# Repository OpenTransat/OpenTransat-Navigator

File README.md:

# OpenTransat-Navigator
The brain of the boat responsible for navigation.

## Features

* Based on Atmega2560 @ 16 MHz

* Over-the-air programming using ESP8266 flashed with Wifi-serial bridge [esp-link](https://github.com/jeelabs/esp-link)

* 9-axis accelerometer / gyro / compass

* Voltage / current sensor

* 16 Mbit flash

* 2 Mbit FRAM

* Temperature / pressure / humidity sensor

* Serial multiplexer

## Boat Hardware Scheme

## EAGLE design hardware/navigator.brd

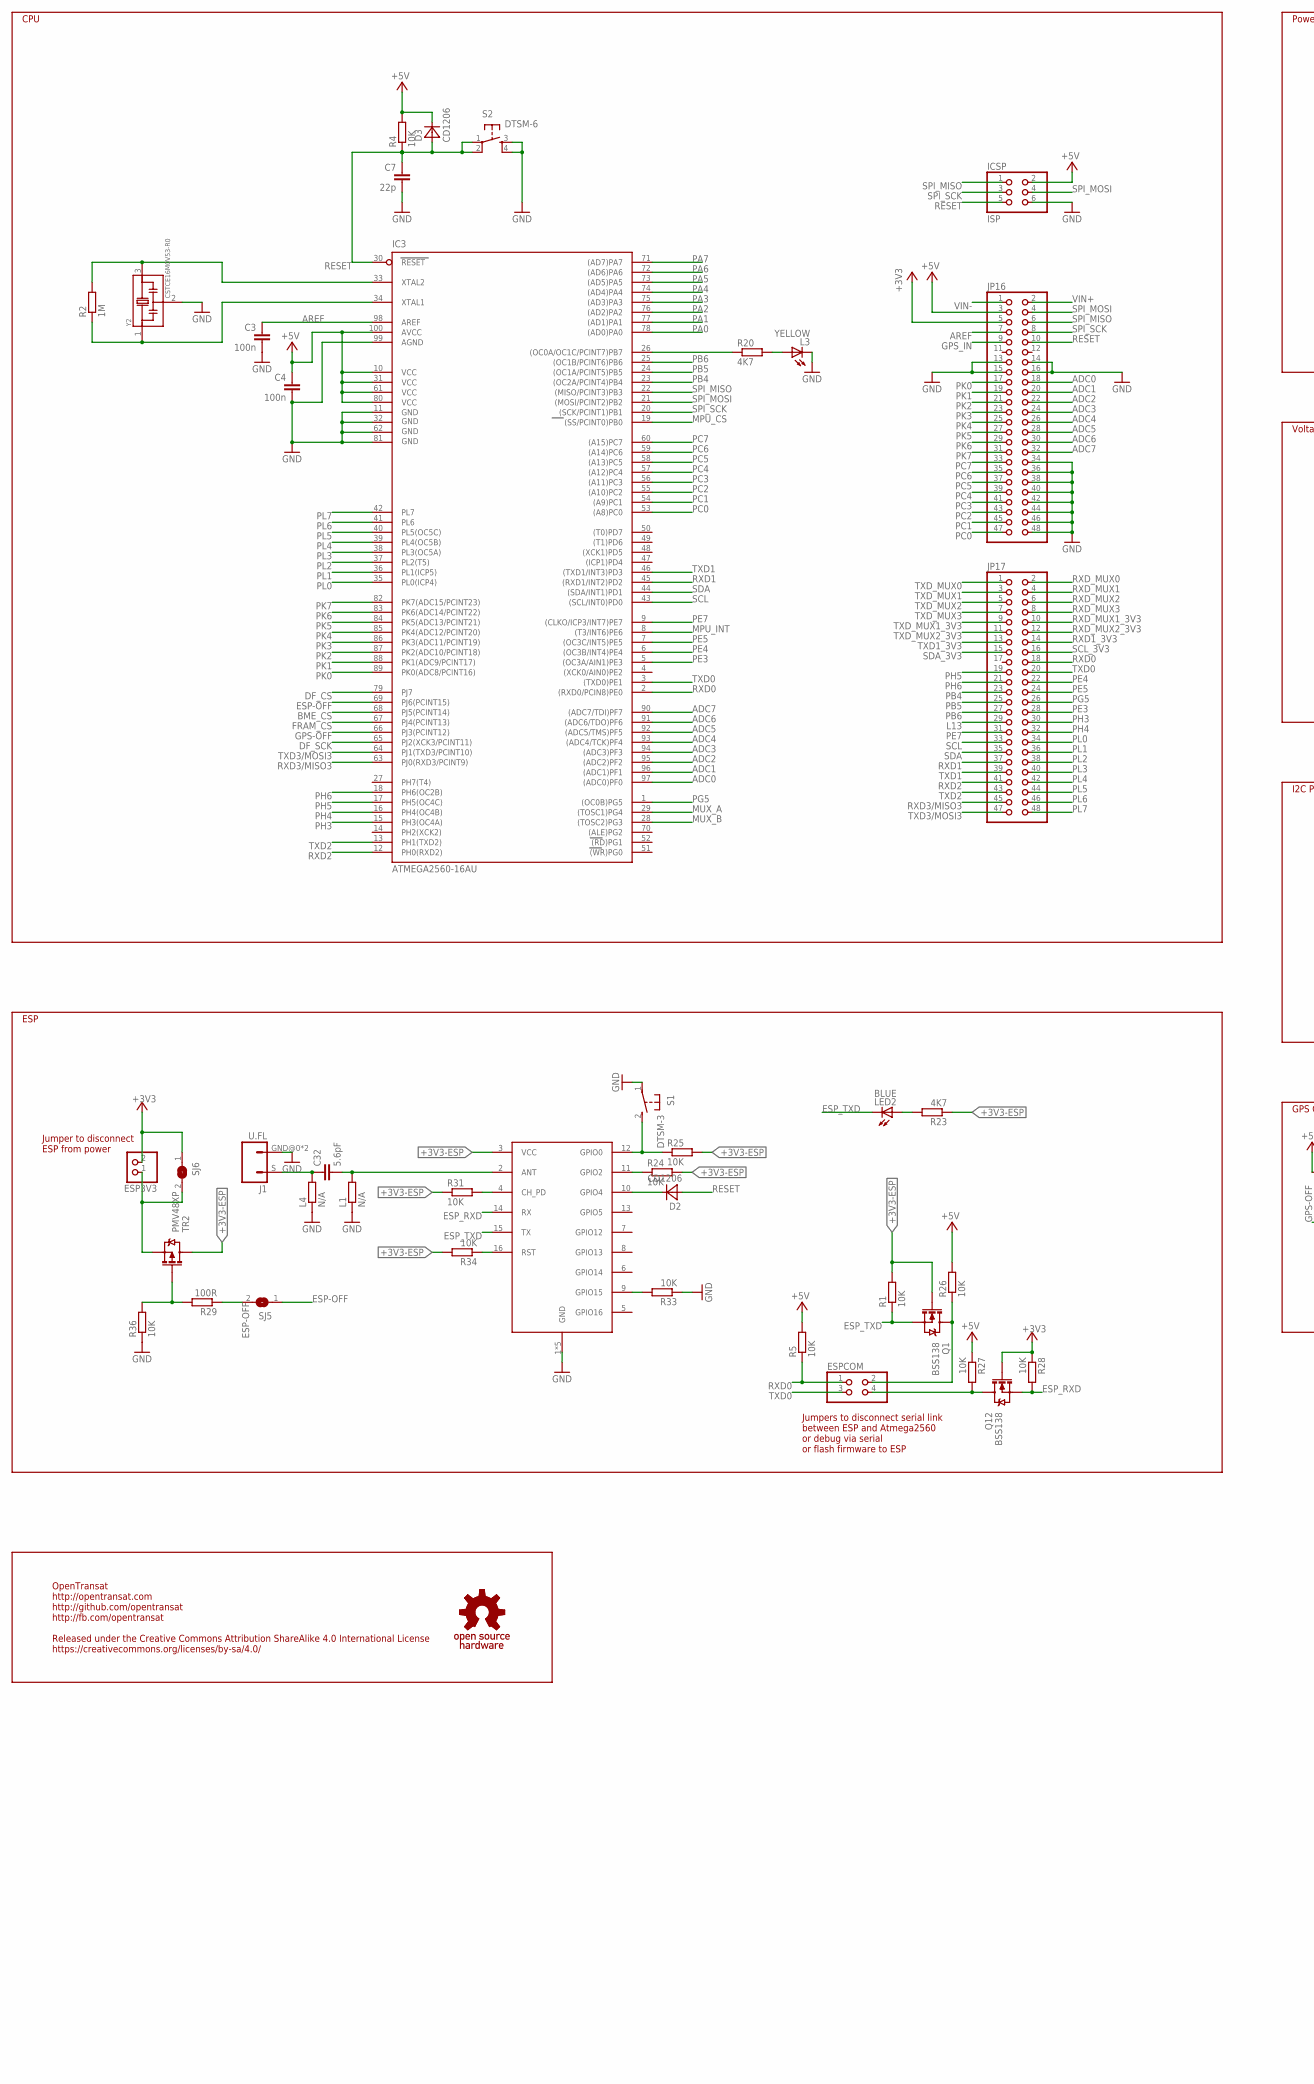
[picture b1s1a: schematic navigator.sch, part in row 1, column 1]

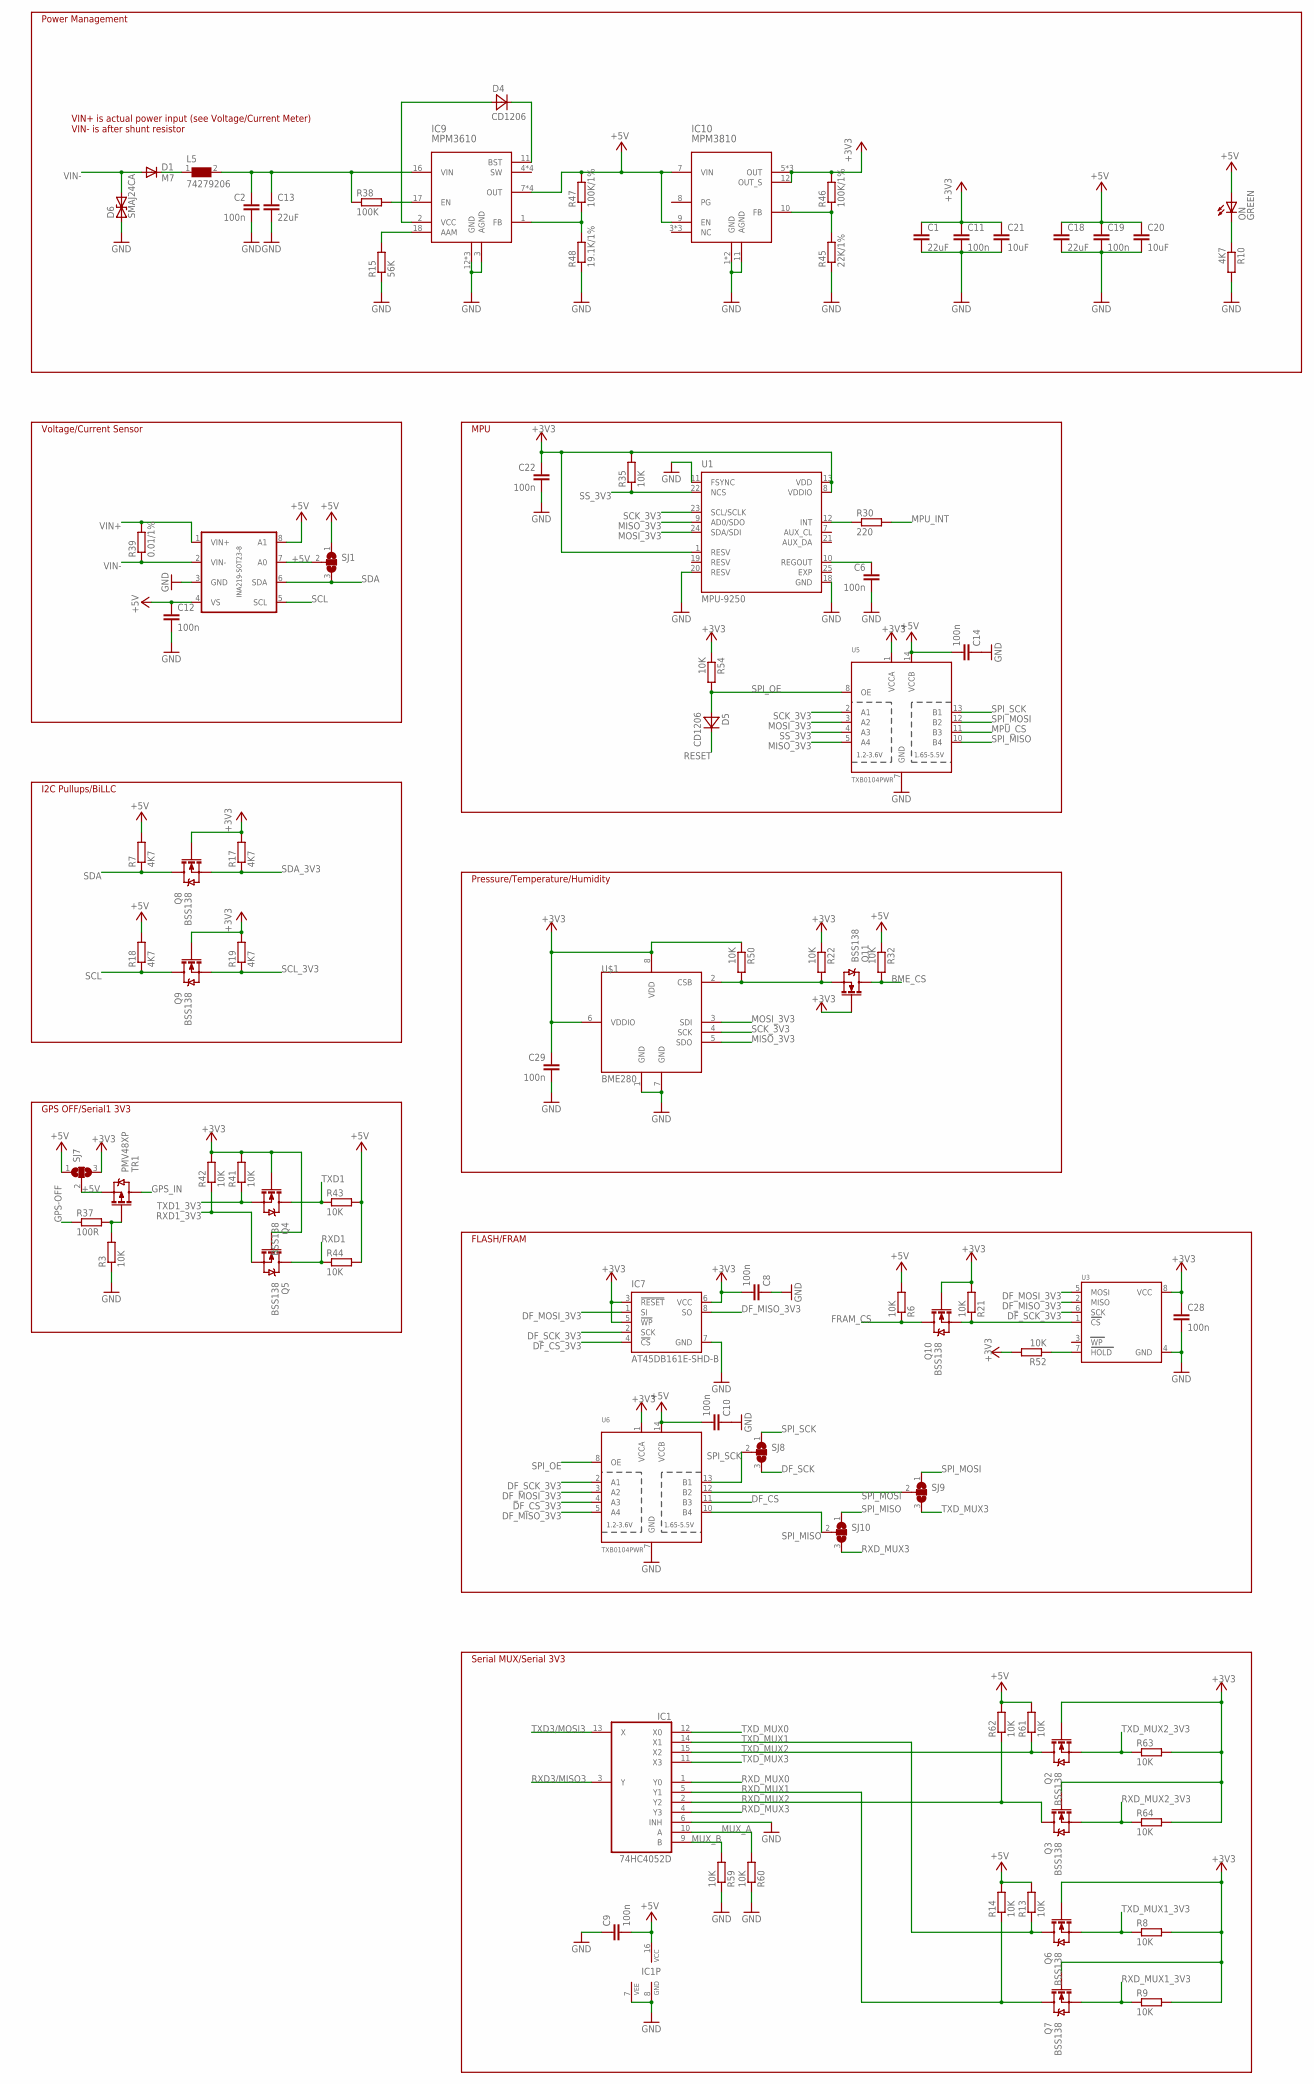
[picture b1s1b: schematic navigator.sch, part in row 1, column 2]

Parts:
C1, C13, C18: 22uF; C1210
C2, C3, C4, C6, C8, C9, C10, C11, C12, C14, C19, C22, C28, C29: 100n; C0603
C7: 22p; C0603
C20, C21: 10uF; C1206
C32: 5.6pF; C0603
D1: M7; DO-214AC
D2, D3, D4, D5: CD1206; R1206
D6: SMAJ24CA; DO214AC
ESP3V3: PINHD-1X2; 1X02
ESPCOM: PINHD-2X2; 2X02
IC1: 74HC4052D; SO16
IC3: ATMEGA2560-16AU; TQFP100
IC7: AT45DB161E-SHD-B; 8S2
IC9: MPM3610; MPM_QFN20
IC10: MPM3810; MPM_QFN12
ICSP: ISP; 2X03
J1: U.FL; CON-U.FL
JP16, JP17: PINHD-2X24; 2X24
L1, L4: N/A; R0402
L3: YELLOW; CHIPLED_0805
L5: 74279206; 0805
LED2: BLUE; CHIPLED_0805
ON: GREEN; CHIPLED_0805
Q1, Q2, Q3, Q4, Q5, Q6, Q7, Q8, Q9, Q10, Q11, Q12: BSS138; SOT23-3
R1, R3, R4, R5, R6, R8, R9, R13, R14, R21, R22, R24, R25, R26, R27, R28, R31, R32, R33, R34, R35, R36, R41, R42, R43, R44, R50, R52, R54, R59, R60, R61, R62, R63, R64: 10K; R0603
R2: 1M; R0603
R7, R10, R17, R18, R19, R20, R23: 4K7; R0603
R15: 56K; R0603
R29, R37: 100R; R0603
R30: 220; R0603
R38: 100K; R0603
R39: 0.01/1%; R2512
R45: 22K/1%; R0603
R46, R47: 100K/1%; R0603
R48: 19.1K/1%; R0603
S1: DTSM-3
S2: DTSM-6
SJ1, SJ7, SJ8, SJ9, SJ10: SJ2W; SJ_2
SJ5, SJ6: SJ
TR1, TR2: PMV48XP; SOT23-3
U1: MPU-9250; QFN40P300X300X105-25N
U3: FRAM_SOIC8_200MIL_SPI; SOIC8_200MIL
U5, U6: TXB0104PWR; TSSOP14
U$1: BME280
U$2: ESP-06
U$3: INA219-SOT23-8; SOT23-8
U$4: OSHW; OSHWM
Y2: CSTCE16M0V53-R0; OSC_CSTCE16M0V53-R0

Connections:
+3V3: C1.1, C8.2, C11.1, C21.1, C22.1, C28.1, C29.1, ESP3V3.2, IC7.3 (!RESET), IC7.5 (!WP), IC7.6 (VCC), IC10.5 (OUT), IC10.6 (OUT), IC10.12 (OUT_S), IC10.14 (OUT), JP16.5, Q2.1 (G), Q3.1 (G), Q4.1 (G), Q5.1 (G), Q6.1 (G), Q7.1 (G), Q8.1 (G), Q9.1 (G), Q10.1 (G), Q11.1 (G), Q12.1 (G), R8.2, R9.2, R17.2, R19.2, R21.2, R22.1, R28.1, R35.2, R41.2, R42.2, R46.2, R50.1, R52.2, R54.1, R63.2, R64.2, SJ6.1, SJ7.3, U1.1 (RESV), U1.8 (VDDIO), U1.13 (VDD), U3.8 (VCC), U5.1 (VCCA), U6.1 (VCCA), U$1.6 (VDDIO), U$1.8 (VDD)
+3V3-ESP: Q1.1 (G), R1.2, R23.1, R24.2, R25.2, R31.1, R34.2, TR2.3 (D), U$2.3 (VCC)
+5V: C4.1, C9.2, C10.2, C12.1, C14.2, C18.1, C19.1, C20.1, D3.2 (C), IC1.16 (VCC), IC3.10 (VCC), IC3.31 (VCC1), IC3.61 (VCC2), IC3.80 (VCC3), IC3.100 (AVCC), IC9.7 (OUT), IC9.8 (OUT), IC9.9 (OUT), IC9.20 (OUT), IC10.7 (VIN), IC10.9 (EN), ICSP.2, JP16.3, ON.A, R4.2, R5.2, R6.2, R7.2, R13.2, R14.2, R18.2, R26.2, R27.1, R32.1, R43.2, R44.2, R47.2, R61.2, R62.2, SJ1.1, SJ1.2, SJ7.1, SJ7.2, TR1.2 (S), U5.14 (VCCB), U6.14 (VCCB), U$3.4 (VS), U$3.7 (A0), U$3.8 (A1)
ADC0: IC3.97 ((ADC0)PF0), JP16.18
ADC1: IC3.96 ((ADC1)PF1), JP16.20
ADC2: IC3.95 ((ADC2)PF2), JP16.22
ADC3: IC3.94 ((ADC3)PF3), JP16.24
ADC4: IC3.93 ((ADC4/TCK)PF4), JP16.26
ADC5: IC3.92 ((ADC5/TMS)PF5), JP16.28
ADC6: IC3.91 ((ADC6/TDO)PF6), JP16.30
ADC7: IC3.90 ((ADC7/TDI)PF7), JP16.32
AREF: C3.1, IC3.98 (AREF), JP16.7
BME_CS: IC3.68 (PJ5(PCINT14)), Q11.3 (D), R32.2
DF_CS: IC3.79 (PJ7), U6.11 (B3)
DF_CS_3V3: IC7.4 (!CS), U6.4 (A3)
DF_MISO_3V3: IC7.8 (SO), U3.2 (MISO), U6.5 (A4)
DF_MOSI_3V3: IC7.1 (SI), U3.5 (MOSI), U6.3 (A2)
DF_SCK: IC3.65 (PJ2(XCK3/PCINT11)), SJ8.3
DF_SCK_3V3: IC7.2 (SCK), U3.6 (SCK), U6.2 (A1)
ESP-OFF: IC3.69 (PJ6(PCINT15)), R29.1, SJ5.1, SJ5.2
ESP_RXD: Q12.2 (S), R28.2, U$2.14 (RX)
ESP_TXD: LED2.C, Q1.2 (S), R1.1, U$2.15 (TX)
EXP: U1.25 (EXP)
FRAM_CS: IC3.67 (PJ4(PCINT13)), Q10.3 (D), R6.1
GND: C1.2, C2.2, C3.2, C4.2, C6.2, C7.2, C8.1, C9.1, C10.1, C11.2, C12.2, C13.2, C14.1, C18.2, C19.2, C20.2, C21.2, C22.2, C28.2, C29.2, D6.A (1), IC1.6 (INH), IC1.7 (VEE), IC1.8 (GND), IC3.11 (GND), IC3.32 (GND1), IC3.62 (GND2), IC3.81 (GND3), IC3.99 (AGND), IC7.7 (GND), IC9.3 (AGND), IC9.12 (GND), IC9.13 (GND), IC9.14 (GND), IC10.1 (GND), IC10.2 (GND), IC10.11 (AGND), ICSP.6, J1.GND@0 (2), J1.GND@1 (2), JP16.13, JP16.14, JP16.15, JP16.16, JP16.34, JP16.36, JP16.38, JP16.40, JP16.42, JP16.44, JP16.46, JP16.48, L1.1, L3.C, L4.1, R3.1, R10.2, R15.1, R33.1, R36.1, R45.1, R48.1, R59.1, R60.1, S1.1, S2.3, S2.4, U1.11 (FSYNC), U1.18 (GND), U1.20 (RESV), U3.4 (GND), U5.7 (GND), U6.7 (GND), U$1.1 (GND), U$1.7 (GND), U$2.1 (GND), U$2.17 (GND), U$2.18 (GND), U$2.19 (GND), U$2.20 (GND), U$3.3 (GND), Y2.2
GPS-OFF: IC3.66 (PJ3(PCINT12)), R37.1
GPS_IN: JP16.9, TR1.3 (D)
L13: IC3.26 ((OC0A/OC1C/PCINT7)PB7), JP17.29, R20.1
MISO_3V3: U1.9 (AD0/SDO), U5.5 (A4), U$1.5 (SDO)
MOSI_3V3: U1.24 (SDA/SDI), U5.3 (A2), U$1.3 (SDI)
MPU_CS: IC3.19 ((SS/PCINT0)PB0), U5.11 (B3)
MPU_INT: IC3.8 ((T3/INT6)PE6), R30.2
MUX_A: IC1.10 (A), IC3.29 ((TOSC1)PG4), R60.2
MUX_B: IC1.9 (B), IC3.28 ((TOSC2)PG3), R59.2
unnamed: ESP3V3.1, SJ6.2, TR2.2 (S)
unnamed: R52.1, U3.7 (HOLD)
unnamed: ON.C, R10.1
unnamed: L3.A, R20.2
unnamed: D4.1 (A), IC9.2 (VCC)
unnamed: D4.2 (C), IC9.11 (BST)
unnamed: LED2.A, R23.2
unnamed: R31.2, U$2.4 (CH_PD)
unnamed: R24.1, U$2.11 (GPIO2)
unnamed: D2.2 (C), U$2.10 (GPIO4)
unnamed: R33.2, U$2.9 (GPIO15)
unnamed: C32.1, J1.S (1), L4.2
unnamed: R25.1, S1.2, U$2.12 (GPIO0)
unnamed: R34.1, U$2.16 (RST)
unnamed: C32.2, L1.2, U$2.2 (ANT)
unnamed: Q10.2 (S), R21.1, U3.1 (CS)
unnamed: IC10.10 (FB), R45.2, R46.1
unnamed: ESPCOM.2, Q1.3 (D), R26.1
unnamed: ESPCOM.4, Q12.3 (D), R27.2
unnamed: R3.2, R37.2, TR1.1 (G)
unnamed: R29.2, R36.2, TR2.1 (G)
unnamed: IC9.1 (FB), R47.1, R48.2
unnamed: IC9.17 (EN), R38.2
unnamed: IC9.18 (AAM), R15.2
unnamed: Q11.2 (S), R22.2, R50.2, U$1.2 (CSB)
unnamed: R30.1, U1.12 (INT)
PA0: IC3.78 ((AD0)PA0)
PA1: IC3.77 ((AD1)PA1)
PA2: IC3.76 ((AD2)PA2)
PA3: IC3.75 ((AD3)PA3)
PA4: IC3.74 ((AD4)PA4)
PA5: IC3.73 ((AD5)PA5)
PA6: IC3.72 ((AD6)PA6)
PA7: IC3.71 ((AD7)PA7)
PB4: IC3.23 ((OC2A/PCINT4)PB4), JP17.23
PB5: IC3.24 ((OC1A/PCINT5)PB5), JP17.25
PB6: IC3.25 ((OC1B/PCINT6)PB6), JP17.27
PC0: IC3.53 ((A8)PC0), JP16.47
PC1: IC3.54 ((A9)PC1), JP16.45
PC2: IC3.55 ((A10)PC2), JP16.43
PC3: IC3.56 ((A11)PC3), JP16.41
PC4: IC3.57 ((A12)PC4), JP16.39
PC5: IC3.58 ((A13)PC5), JP16.37
PC6: IC3.59 ((A14)PC6), JP16.35
PC7: IC3.60 ((A15)PC7), JP16.33
PE3: IC3.5 ((OC3A/AIN1)PE3), JP17.28
PE4: IC3.6 ((OC3B/INT4)PE4), JP17.22
PE5: IC3.7 ((OC3C/INT5)PE5), JP17.24
PE7: IC3.9 ((CLKO/ICP3/INT7)PE7), JP17.31
PG5: IC3.1 ((OC0B)PG5), JP17.26
PH3: IC3.15 (PH3(OC4A)), JP17.30
PH4: IC3.16 (PH4(OC4B)), JP17.32
PH5: IC3.17 (PH5(OC4C)), JP17.19
PH6: IC3.18 (PH6(OC2B)), JP17.21
PK0: IC3.89 (PK0(ADC8/PCINT16)), JP16.17
PK1: IC3.88 (PK1(ADC9/PCINT17)), JP16.19
PK2: IC3.87 (PK2(ADC10/PCINT18)), JP16.21
PK3: IC3.86 (PK3(ADC11/PCINT19)), JP16.23
PK4: IC3.85 (PK4(ADC12/PCINT20)), JP16.25
PK5: IC3.84 (PK5(ADC13/PCINT21)), JP16.27
PK6: IC3.83 (PK6(ADC14/PCINT22)), JP16.29
PK7: IC3.82 (PK7(ADC15/PCINT23)), JP16.31
PL0: IC3.35 (PL0(ICP4)), JP17.34
PL1: IC3.36 (PL1(ICP5)), JP17.36
PL2: IC3.37 (PL2(T5)), JP17.38
PL3: IC3.38 (PL3(OC5A)), JP17.40
PL4: IC3.39 (PL4(OC5B)), JP17.42
PL5: IC3.40 (PL5(OC5C)), JP17.44
PL6: IC3.41 (PL6), JP17.46
PL7: IC3.42 (PL7), JP17.48
PWRIN2: D1.C, L5.1
REGOUT: C6.1, U1.10 (REGOUT)
RESET: C7.1, D2.1 (A), D3.1 (A), D5.2 (C), IC3.30 (RESET), ICSP.5, JP16.10, R4.1, S2.1, S2.2
RESV: U1.19 (RESV)
RXD0: ESPCOM.1, IC3.2 ((RXD0/PCIN8)PE0), JP17.18, R5.1
RXD1: IC3.45 ((RXD1/INT2)PD2), JP17.37, Q5.3 (D), R44.1
RXD1_3V3: JP17.14, Q5.2 (S), R42.1
RXD2: IC3.12 (PH0(RXD2)), JP17.41
RXD3/MISO3: IC1.3 (Y), IC3.63 (PJ0(RXD3/PCINT9)), JP17.45
RXD_MUX0: IC1.1 (Y0), JP17.2
RXD_MUX1: IC1.5 (Y1), JP17.4, Q7.3 (D), R14.1
RXD_MUX1_3V3: JP17.10, Q7.2 (S), R9.1
RXD_MUX2: IC1.2 (Y2), JP17.6, Q3.3 (D), R62.1
RXD_MUX2_3V3: JP17.12, Q3.2 (S), R64.1
RXD_MUX3: IC1.4 (Y3), JP17.8, SJ10.3
SCK_3V3: U1.23 (SCL/SCLK), U5.2 (A1), U$1.4 (SCK)
SCL: IC3.43 ((SCL/INT0)PD0), JP17.33, Q9.3 (D), R18.1, U$3.5 (SCL)
SCL_3V3: JP17.16, Q9.2 (S), R19.1
SDA: IC3.44 ((SDA/INT1)PD1), JP17.35, Q8.3 (D), R7.1, SJ1.3, U$3.6 (SDA)
SDA_3V3: JP17.15, Q8.2 (S), R17.1
SPI_MISO: IC3.22 ((MISO/PCINT3)PB3), ICSP.1, JP16.6, SJ10.1, SJ10.2, U5.10 (B4), U6.10 (B4)
SPI_MOSI: IC3.21 ((MOSI/PCINT2)PB2), ICSP.4, JP16.4, SJ9.1, SJ9.2, U5.12 (B2), U6.12 (B2)
SPI_OE: D5.1 (A), R54.2, U5.8 (OE), U6.8 (OE)
SPI_SCK: IC3.20 ((SCK/PCINT1)PB1), ICSP.3, JP16.8, SJ8.1, SJ8.2, U5.13 (B1), U6.13 (B1)
SS_3V3: R35.1, U1.22 (NCS), U5.4 (A3)
TXD0: ESPCOM.3, IC3.3 ((TXD0)PE1), JP17.20
TXD1: IC3.46 ((TXD1/INT3)PD3), JP17.39, Q4.3 (D), R43.1
TXD1_3V3: JP17.13, Q4.2 (S), R41.1
TXD2: IC3.13 (PH1(TXD2)), JP17.43
TXD3/MOSI3: IC1.13 (X), IC3.64 (PJ1(TXD3/PCINT10)), JP17.47
TXD_MUX0: IC1.12 (X0), JP17.1
TXD_MUX1: IC1.14 (X1), JP17.3, Q6.3 (D), R13.1
TXD_MUX1_3V3: JP17.9, Q6.2 (S), R8.1
TXD_MUX2: IC1.15 (X2), JP17.5, Q2.3 (D), R61.1
TXD_MUX2_3V3: JP17.11, Q2.2 (S), R63.1
TXD_MUX3: IC1.11 (X3), JP17.7, SJ9.3
VIN: C2.1, C13.1, IC9.16 (VIN), L5.2, R38.1
VIN+: JP16.2, R39.2, U$3.1 (VIN+)
VIN-: D1.A, D6.C (2), JP16.1, R39.1, U$3.2 (VIN-)
XTAL1: IC3.34 (XTAL1), R2.1, Y2.1
XTAL2: IC3.33 (XTAL2), R2.2, Y2.3

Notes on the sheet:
Serial MUX/Serial 3V3
Voltage/Current Sensor
GPS OFF/Serial1 3V3
FLASH/FRAM
MPU
Pressure/Temperature/Humidity
ESP
CPU
Power Management
I2C Pullups/BiLLC
VIN+ is actual power input (see Voltage/Current Meter) VIN- is after shunt resistor
OpenTransat http://opentransat.com http://github.com/opentransat http://fb.com/opentransat Released under the Creative Commons Attribution ShareAlike 4.0 International License https://creativecommons.org/licenses/by-sa/4.0/
Jumper to disconnect ESP from power
Jumpers to disconnect serial link between ESP and Atmega2560 or debug via serial or flash firmware to ESP

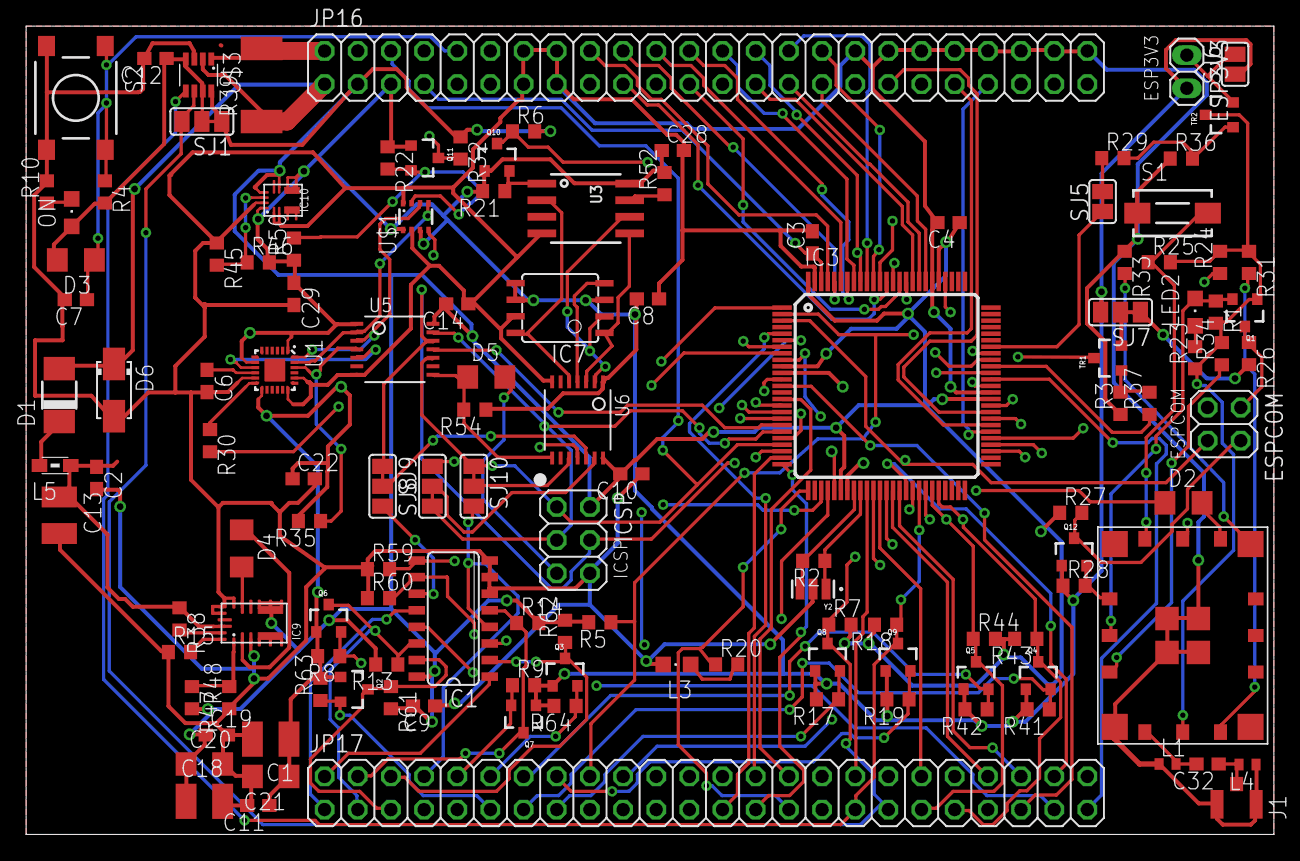
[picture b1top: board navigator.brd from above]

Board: 4 copper layers, 95.6 x 61.9 mm, 129 parts (0 on the bottom side), 135 nets.

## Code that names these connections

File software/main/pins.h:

//pin definitions
#define LED 13 //PB7
#define MPU_CS 53 //PB0
#define MPU_INT 70 //PE6
#define FRAM_CS 73 //PJ4
#define DF_CS 76 //PJ7
#define BME_CS 74 //PJ5
#define GPS_OFF 72 //PJ3
#define ESP_OFF 75 //PJ6
#define MUX_A 77 //PG4
#define MUX_B 78 //PG3
#define RC_PWM0 2 //PE4
#define RC_PWM1 3 //PE5
#define RC_PWM2 79 //PE7
#define RC_PWM3 62 //PK0
#define HEARTBEAT 32 //PC5
#define WARNING 33 //PC4
#define RC_OFF 34 //PC3
#define AIS_OFF 35 //PC2
#define IR_SLEEP 36 //PC1
#define CAM_ON 37 //PC0
#define AUX_ON 8 //PH5
#define ENC_CLK 9 //PH6
#define ENC_CS 10 //PB4
#define ENC_OUT 11 //PB5
#define TMP 12 //PB6
#define M3_REV 49 //PL0
#define M3_ON 48 //PL1
#define M2_ON 47 //PL2
#define M1_ON 46 //PL3
#define M2_PWM 45 //PL4
#define M1_PWM 44 //PL5
#define SAT_ON 42 //PL7
#define PWRSENSOR_ON 31 //PC6
#define FLOOD0 56 //PF2
#define FLOOD1 57 //PF3
#define PUMP1_ON 63 //PK1
#define PUMP2_ON 64 //PK2
#define PK3 65 //PK3
#define PIN_UNUSED0 41 //PG0, anemo TX
#define PIN_UNUSED1 40 //PG1, rudder TX

//pin modifications
#define ACT_ON M2_ON
#define LED_EXT M2_PWM
#define HALL_ON M1_ON
#define CAM_RX ENC_CS //has pin change interrupts
#define CAM_TX ENC_CLK
#define ANEMO_RX PK3 //has pin change interrupts
#define ANEMO_TX PIN_UNUSED0
#define RUDDER_RX ENC_OUT //has pin change interrupts
#define RUDDER_TX PIN_UNUSED1

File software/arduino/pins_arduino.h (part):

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#define digitalPinHasPWM(p)         (((p) >= 2 && (p) <= 13) || ((p) >= 44 && (p)<= 46))

#define PIN_SPI_SS    (53)
#define PIN_SPI_MOSI  (51)
#define PIN_SPI_MISO  (50)
#define PIN_SPI_SCK   (52)

static const uint8_t SS   = PIN_SPI_SS;
static const uint8_t MOSI = PIN_SPI_MOSI;
static const uint8_t MISO = PIN_SPI_MISO;
static const uint8_t SCK  = PIN_SPI_SCK;

#define PIN_WIRE_SDA        (20)
#define PIN_WIRE_SCL        (21)
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
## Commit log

2020-01-20 the first commit

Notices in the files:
software/arduino/pins_arduino.h:
Copyright (c) 2007 David A. Mellis
Public License along with this library; if not, write to the
Free Software Foundation, Inc., 59 Temple Place, Suite 330,
Boston, MA  02111-1307  USA
parts and their libraries:
Wurth_Elektronik_Passive_rev15b: Copyright: Würth Elektronik
m-pad-2.1: License : GNU General Public License version 2 (see bottom)
SparkFun-Aesthetics: Licensing: Creative Commons ShareAlike 4.0 International - https://creativecommons.org/licenses/by-sa/4.0
